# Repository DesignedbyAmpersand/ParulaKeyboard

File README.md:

Parula is a 100x49mm USB keyboard with 66 keys.

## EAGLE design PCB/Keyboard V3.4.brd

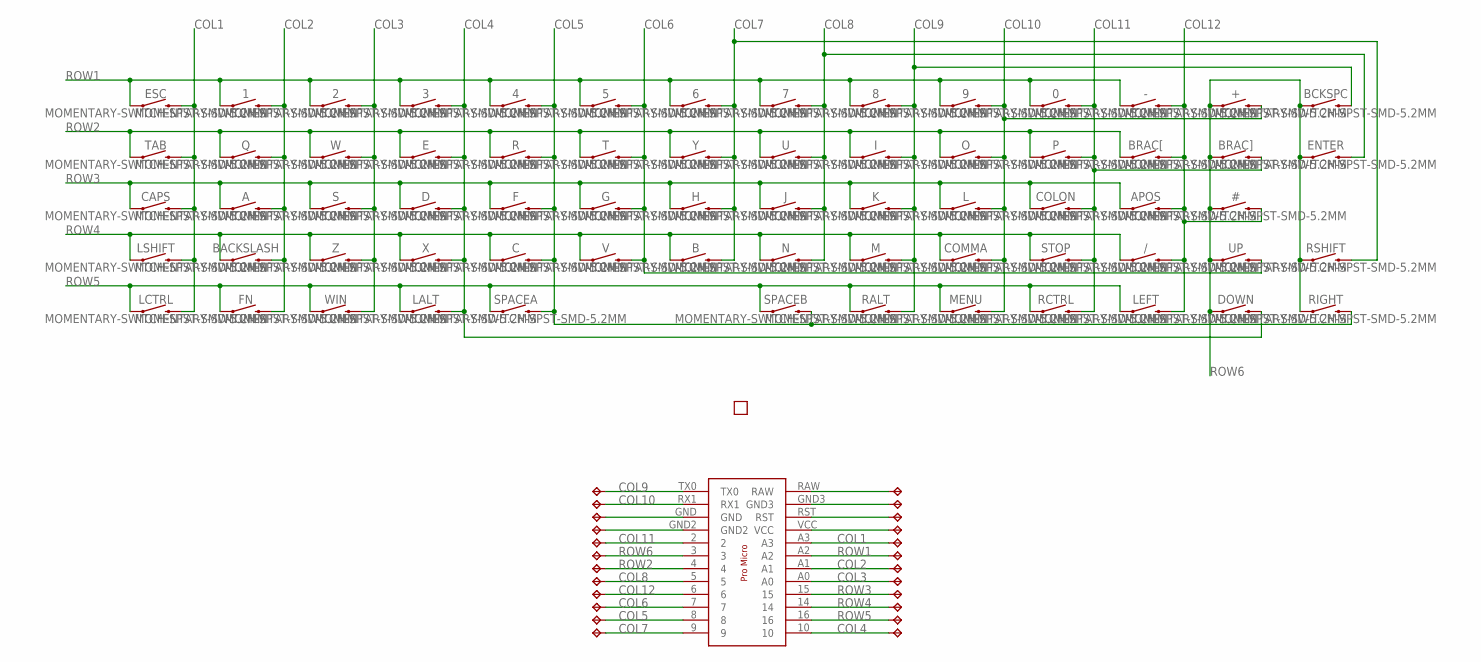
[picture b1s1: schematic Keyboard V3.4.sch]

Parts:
0, 1, 2, 3, 4, 5, 6, 7, 8, 9: MOMENTARY-SWITCH-SPST-SMD-5.2MM; TACTILE_SWITCH_SMD_5.2MM
#: MOMENTARY-SWITCH-SPST-SMD-5.2MM; TACTILE_SWITCH_SMD_5.2MM
+: MOMENTARY-SWITCH-SPST-SMD-5.2MM; TACTILE_SWITCH_SMD_5.2MM
-: MOMENTARY-SWITCH-SPST-SMD-5.2MM; TACTILE_SWITCH_SMD_5.2MM
/: MOMENTARY-SWITCH-SPST-SMD-5.2MM; TACTILE_SWITCH_SMD_5.2MM
A: MOMENTARY-SWITCH-SPST-SMD-5.2MM; TACTILE_SWITCH_SMD_5.2MM
APOS: MOMENTARY-SWITCH-SPST-SMD-5.2MM; TACTILE_SWITCH_SMD_5.2MM
B: MOMENTARY-SWITCH-SPST-SMD-5.2MM; TACTILE_SWITCH_SMD_5.2MM
BACKSLASH: MOMENTARY-SWITCH-SPST-SMD-5.2MM; TACTILE_SWITCH_SMD_5.2MM
BCKSPC: MOMENTARY-SWITCH-SPST-SMD-5.2MM; TACTILE_SWITCH_SMD_5.2MM
BRAC[: MOMENTARY-SWITCH-SPST-SMD-5.2MM; TACTILE_SWITCH_SMD_5.2MM
BRAC]: MOMENTARY-SWITCH-SPST-SMD-5.2MM; TACTILE_SWITCH_SMD_5.2MM
C: MOMENTARY-SWITCH-SPST-SMD-5.2MM; TACTILE_SWITCH_SMD_5.2MM
CAPS: MOMENTARY-SWITCH-SPST-SMD-5.2MM; TACTILE_SWITCH_SMD_5.2MM
COLON: MOMENTARY-SWITCH-SPST-SMD-5.2MM; TACTILE_SWITCH_SMD_5.2MM
COMMA: MOMENTARY-SWITCH-SPST-SMD-5.2MM; TACTILE_SWITCH_SMD_5.2MM
D: MOMENTARY-SWITCH-SPST-SMD-5.2MM; TACTILE_SWITCH_SMD_5.2MM
DOWN: MOMENTARY-SWITCH-SPST-SMD-5.2MM; TACTILE_SWITCH_SMD_5.2MM
E: MOMENTARY-SWITCH-SPST-SMD-5.2MM; TACTILE_SWITCH_SMD_5.2MM
ENTER: MOMENTARY-SWITCH-SPST-SMD-5.2MM; TACTILE_SWITCH_SMD_5.2MM
ESC: MOMENTARY-SWITCH-SPST-SMD-5.2MM; TACTILE_SWITCH_SMD_5.2MM
F: MOMENTARY-SWITCH-SPST-SMD-5.2MM; TACTILE_SWITCH_SMD_5.2MM
FN: MOMENTARY-SWITCH-SPST-SMD-5.2MM; TACTILE_SWITCH_SMD_5.2MM
G: MOMENTARY-SWITCH-SPST-SMD-5.2MM; TACTILE_SWITCH_SMD_5.2MM
H: MOMENTARY-SWITCH-SPST-SMD-5.2MM; TACTILE_SWITCH_SMD_5.2MM
I: MOMENTARY-SWITCH-SPST-SMD-5.2MM; TACTILE_SWITCH_SMD_5.2MM
J: MOMENTARY-SWITCH-SPST-SMD-5.2MM; TACTILE_SWITCH_SMD_5.2MM
K: MOMENTARY-SWITCH-SPST-SMD-5.2MM; TACTILE_SWITCH_SMD_5.2MM
L: MOMENTARY-SWITCH-SPST-SMD-5.2MM; TACTILE_SWITCH_SMD_5.2MM
LALT: MOMENTARY-SWITCH-SPST-SMD-5.2MM; TACTILE_SWITCH_SMD_5.2MM
LCTRL: MOMENTARY-SWITCH-SPST-SMD-5.2MM; TACTILE_SWITCH_SMD_5.2MM
LEFT: MOMENTARY-SWITCH-SPST-SMD-5.2MM; TACTILE_SWITCH_SMD_5.2MM
LSHIFT: MOMENTARY-SWITCH-SPST-SMD-5.2MM; TACTILE_SWITCH_SMD_5.2MM
M: MOMENTARY-SWITCH-SPST-SMD-5.2MM; TACTILE_SWITCH_SMD_5.2MM
MENU: MOMENTARY-SWITCH-SPST-SMD-5.2MM; TACTILE_SWITCH_SMD_5.2MM
N: MOMENTARY-SWITCH-SPST-SMD-5.2MM; TACTILE_SWITCH_SMD_5.2MM
O: MOMENTARY-SWITCH-SPST-SMD-5.2MM; TACTILE_SWITCH_SMD_5.2MM
P: MOMENTARY-SWITCH-SPST-SMD-5.2MM; TACTILE_SWITCH_SMD_5.2MM
Q: MOMENTARY-SWITCH-SPST-SMD-5.2MM; TACTILE_SWITCH_SMD_5.2MM
R: MOMENTARY-SWITCH-SPST-SMD-5.2MM; TACTILE_SWITCH_SMD_5.2MM
RALT: MOMENTARY-SWITCH-SPST-SMD-5.2MM; TACTILE_SWITCH_SMD_5.2MM
RCTRL: MOMENTARY-SWITCH-SPST-SMD-5.2MM; TACTILE_SWITCH_SMD_5.2MM
RIGHT: MOMENTARY-SWITCH-SPST-SMD-5.2MM; TACTILE_SWITCH_SMD_5.2MM
RSHIFT: MOMENTARY-SWITCH-SPST-SMD-5.2MM; TACTILE_SWITCH_SMD_5.2MM
S: MOMENTARY-SWITCH-SPST-SMD-5.2MM; TACTILE_SWITCH_SMD_5.2MM
SPACEA: MOMENTARY-SWITCH-SPST-SMD-5.2MM; TACTILE_SWITCH_SMD_5.2MM
SPACEB: MOMENTARY-SWITCH-SPST-SMD-5.2MM; TACTILE_SWITCH_SMD_5.2MM
STOP: MOMENTARY-SWITCH-SPST-SMD-5.2MM; TACTILE_SWITCH_SMD_5.2MM
T: MOMENTARY-SWITCH-SPST-SMD-5.2MM; TACTILE_SWITCH_SMD_5.2MM
TAB: MOMENTARY-SWITCH-SPST-SMD-5.2MM; TACTILE_SWITCH_SMD_5.2MM
TP1, TP2, TP3, TP4, TP5, TP6, TP7, TP8, TP9, TP10, TP11, TP12, TP13, TP14, TP15, TP16, TP17, TP18, TP19, TP20, TP21, TP22, TP23, TP24: TPTP14R; TP14R
U: MOMENTARY-SWITCH-SPST-SMD-5.2MM; TACTILE_SWITCH_SMD_5.2MM
U$1: PEANUT-PRO-MICRO; PRO-MICRO
U$3: AMP-HALF
UP: MOMENTARY-SWITCH-SPST-SMD-5.2MM; TACTILE_SWITCH_SMD_5.2MM
V: MOMENTARY-SWITCH-SPST-SMD-5.2MM; TACTILE_SWITCH_SMD_5.2MM
W: MOMENTARY-SWITCH-SPST-SMD-5.2MM; TACTILE_SWITCH_SMD_5.2MM
WIN: MOMENTARY-SWITCH-SPST-SMD-5.2MM; TACTILE_SWITCH_SMD_5.2MM
X: MOMENTARY-SWITCH-SPST-SMD-5.2MM; TACTILE_SWITCH_SMD_5.2MM
Y: MOMENTARY-SWITCH-SPST-SMD-5.2MM; TACTILE_SWITCH_SMD_5.2MM
Z: MOMENTARY-SWITCH-SPST-SMD-5.2MM; TACTILE_SWITCH_SMD_5.2MM

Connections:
COL1: CAPS.3 (2), CAPS.4 (2), ESC.3 (2), ESC.4 (2), LCTRL.3 (2), LCTRL.4 (2), LSHIFT.3 (2), LSHIFT.4 (2), TAB.3 (2), TAB.4 (2), TP8.TP, U$1.A3
COL2: 1.3 (2), 1.4 (2), A.3 (2), A.4 (2), BACKSLASH.3 (2), BACKSLASH.4 (2), FN.3 (2), FN.4 (2), Q.3 (2), Q.4 (2), TP6.TP, U$1.A1
COL3: 2.3 (2), 2.4 (2), S.3 (2), S.4 (2), TP5.TP, U$1.A0, W.3 (2), W.4 (2), WIN.3 (2), WIN.4 (2), Z.3 (2), Z.4 (2)
COL4: 3.3 (2), 3.4 (2), D.3 (2), D.4 (2), DOWN.3 (2), DOWN.4 (2), E.3 (2), E.4 (2), LALT.3 (2), LALT.4 (2), TP2.TP, U$1.10, X.3 (2), X.4 (2)
COL5: 4.3 (2), 4.4 (2), C.3 (2), C.4 (2), F.3 (2), F.4 (2), R.3 (2), R.4 (2), RIGHT.3 (2), RIGHT.4 (2), SPACEA.3 (2), SPACEA.4 (2), SPACEB.3 (2), SPACEB.4 (2), TP17.TP, U$1.8
COL6: 5.3 (2), 5.4 (2), G.3 (2), G.4 (2), T.3 (2), T.4 (2), TP16.TP, U$1.7, UP.3 (2), UP.4 (2), V.3 (2), V.4 (2)
COL7: 6.3 (2), 6.4 (2), B.3 (2), B.4 (2), H.3 (2), H.4 (2), RSHIFT.3 (2), RSHIFT.4 (2), TP18.TP, U$1.9, Y.3 (2), Y.4 (2)
COL8: 7.3 (2), 7.4 (2), ENTER.3 (2), ENTER.4 (2), J.3 (2), J.4 (2), N.3 (2), N.4 (2), TP14.TP, U.3 (2), U.4 (2), U$1.5
COL9: 8.3 (2), 8.4 (2), BCKSPC.3 (2), BCKSPC.4 (2), I.3 (2), I.4 (2), K.3 (2), K.4 (2), M.3 (2), M.4 (2), RALT.3 (2), RALT.4 (2), TP9.TP, U$1.TX0
COL10: 9.3 (2), 9.4 (2), +.3 (2), +.4 (2), COMMA.3 (2), COMMA.4 (2), L.3 (2), L.4 (2), MENU.3 (2), MENU.4 (2), O.3 (2), O.4 (2), TP10.TP, U$1.RX1
COL11: 0.3 (2), 0.4 (2), BRAC].3 (2), BRAC].4 (2), COLON.3 (2), COLON.4 (2), P.3 (2), P.4 (2), RCTRL.3 (2), RCTRL.4 (2), STOP.3 (2), STOP.4 (2), TP11.TP, U$1.2
COL12: #.3 (2), #.4 (2), -.3 (2), -.4 (2), /.3 (2), /.4 (2), APOS.3 (2), APOS.4 (2), BRAC[.3 (2), BRAC[.4 (2), LEFT.3 (2), LEFT.4 (2), TP15.TP, U$1.6
unnamed: TP20.TP, U$1.GND
unnamed: TP19.TP, U$1.GND2
unnamed: TP24.TP, U$1.RAW
unnamed: TP23.TP, U$1.GND3
unnamed: TP22.TP, U$1.RST
unnamed: TP21.TP, U$1.VCC
ROW1: 0.1, 0.2 (1), 1.1, 1.2 (1), 2.1, 2.2 (1), 3.1, 3.2 (1), 4.1, 4.2 (1), 5.1, 5.2 (1), 6.1, 6.2 (1), 7.1, 7.2 (1), 8.1, 8.2 (1), 9.1, 9.2 (1), -.1, -.2 (1), ESC.1, ESC.2 (1), TP7.TP, U$1.A2
ROW2: BRAC[.1, BRAC[.2 (1), E.1, E.2 (1), I.1, I.2 (1), O.1, O.2 (1), P.1, P.2 (1), Q.1, Q.2 (1), R.1, R.2 (1), T.1, T.2 (1), TAB.1, TAB.2 (1), TP13.TP, U.1, U.2 (1), U$1.4, W.1, W.2 (1), Y.1, Y.2 (1)
ROW3: A.1, A.2 (1), APOS.1, APOS.2 (1), CAPS.1, CAPS.2 (1), COLON.1, COLON.2 (1), D.1, D.2 (1), F.1, F.2 (1), G.1, G.2 (1), H.1, H.2 (1), J.1, J.2 (1), K.1, K.2 (1), L.1, L.2 (1), S.1, S.2 (1), TP4.TP, U$1.15
ROW4: /.1, /.2 (1), B.1, B.2 (1), BACKSLASH.1, BACKSLASH.2 (1), C.1, C.2 (1), COMMA.1, COMMA.2 (1), LSHIFT.1, LSHIFT.2 (1), M.1, M.2 (1), N.1, N.2 (1), STOP.1, STOP.2 (1), TP3.TP, U$1.14, V.1, V.2 (1), X.1, X.2 (1), Z.1, Z.2 (1)
ROW5: FN.1, FN.2 (1), LALT.1, LALT.2 (1), LCTRL.1, LCTRL.2 (1), LEFT.1, LEFT.2 (1), MENU.1, MENU.2 (1), RALT.1, RALT.2 (1), RCTRL.1, RCTRL.2 (1), SPACEA.1, SPACEA.2 (1), SPACEB.1, SPACEB.2 (1), TP1.TP, U$1.16, WIN.1, WIN.2 (1)
ROW6: #.1, #.2 (1), +.1, +.2 (1), BCKSPC.1, BCKSPC.2 (1), BRAC].1, BRAC].2 (1), DOWN.1, DOWN.2 (1), ENTER.1, ENTER.2 (1), RIGHT.1, RIGHT.2 (1), RSHIFT.1, RSHIFT.2 (1), TP12.TP, U$1.3, UP.1, UP.2 (1)

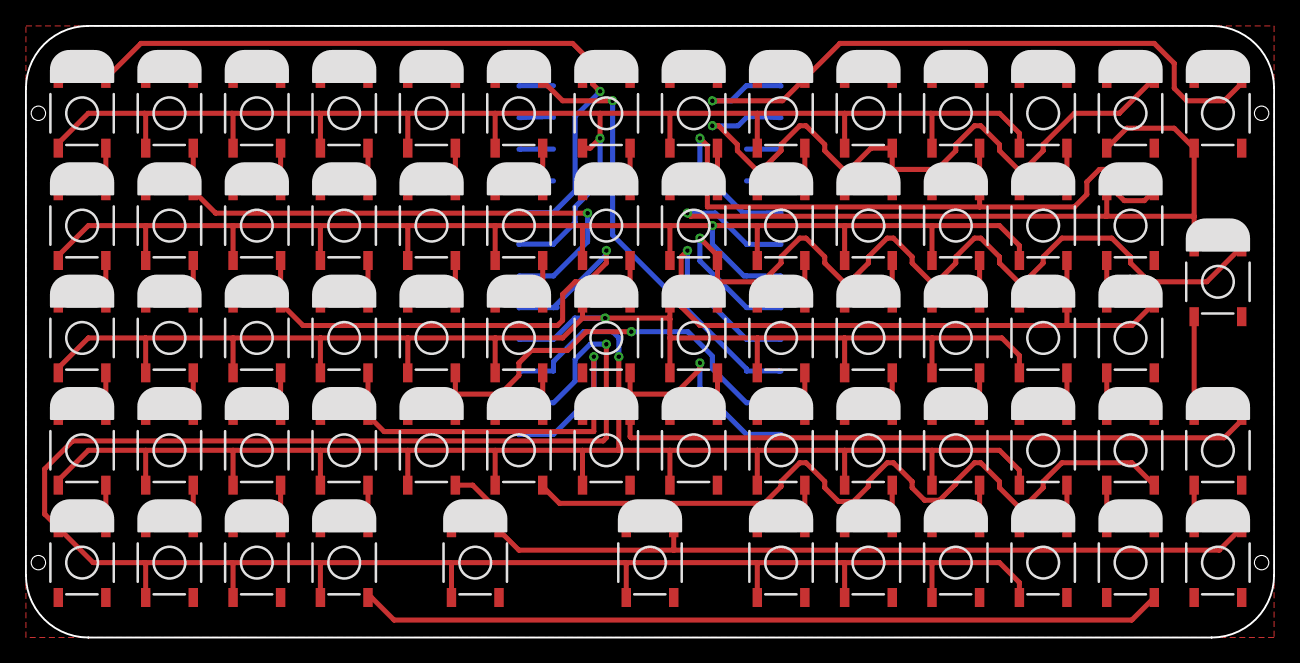
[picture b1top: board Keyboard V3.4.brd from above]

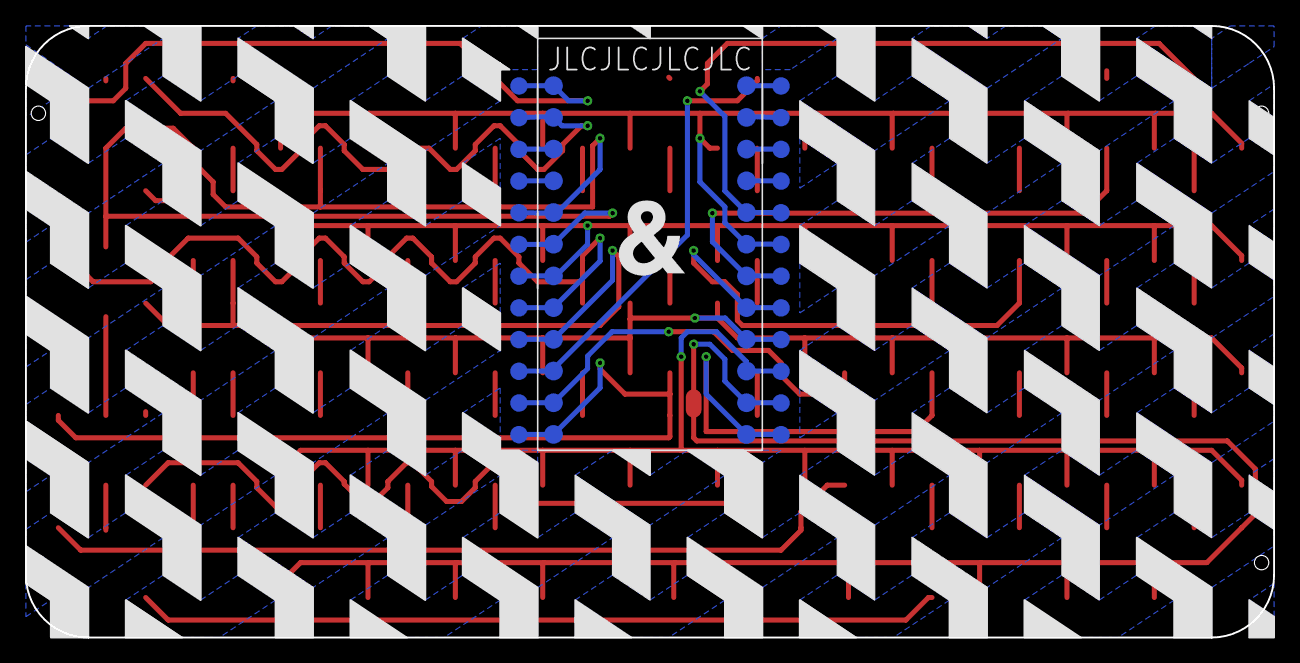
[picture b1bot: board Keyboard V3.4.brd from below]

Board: 2 copper layers, 100.0 x 49.0 mm, 93 parts (26 on the bottom side), 24 nets.

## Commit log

2025-06-03 Add files via upload
    Parula is a 100x49mm USB keyboard with 66 keys.

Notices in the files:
parts and their libraries:
SparkFun-Switches-Edit: Licensing: Creative Commons ShareAlike 4.0 International - https://creativecommons.org/licenses/by-sa/4.0
